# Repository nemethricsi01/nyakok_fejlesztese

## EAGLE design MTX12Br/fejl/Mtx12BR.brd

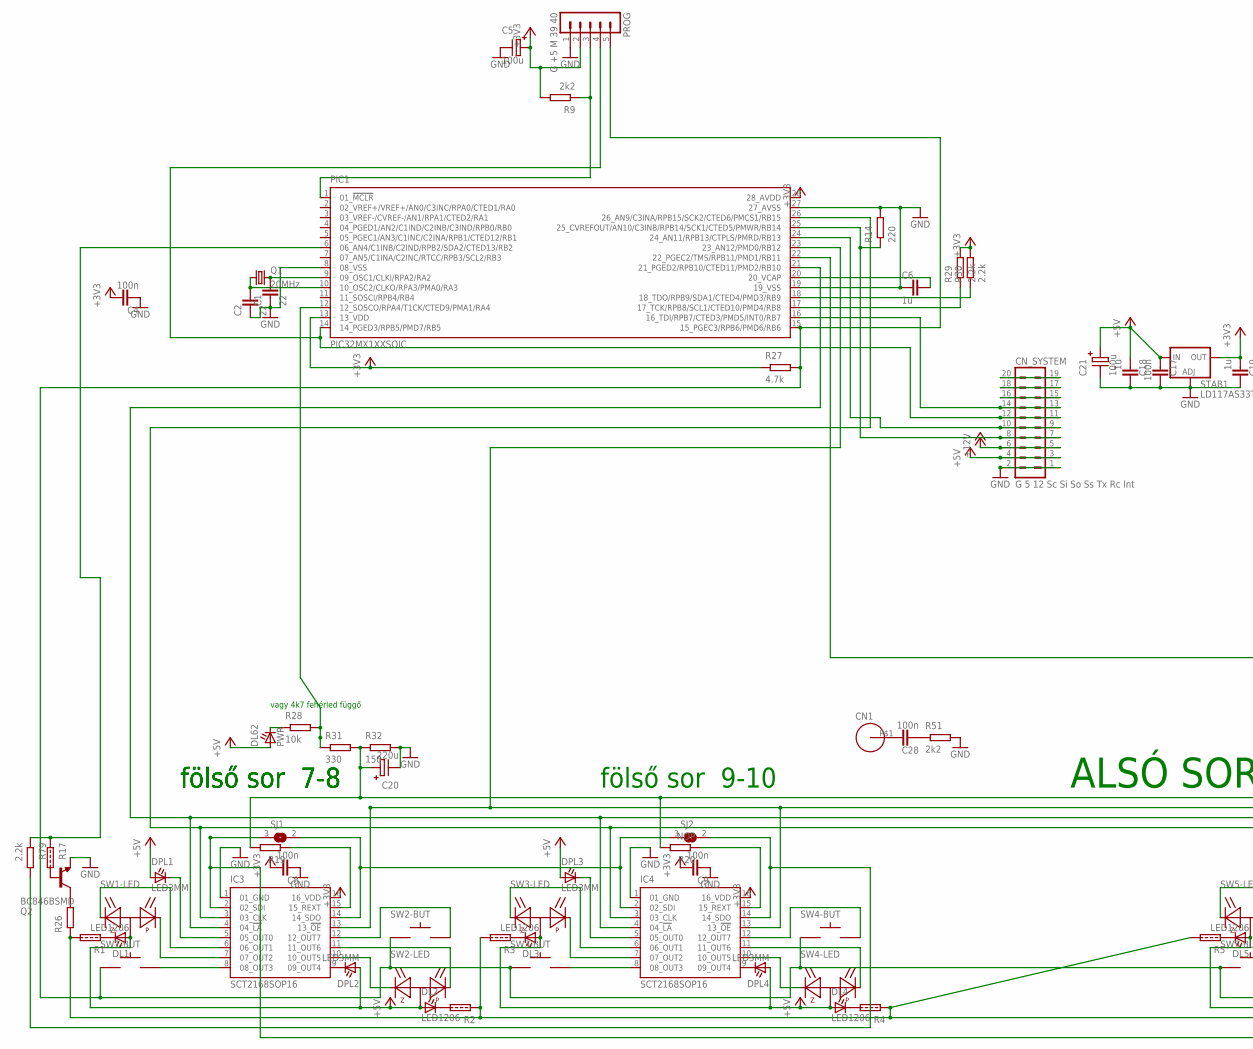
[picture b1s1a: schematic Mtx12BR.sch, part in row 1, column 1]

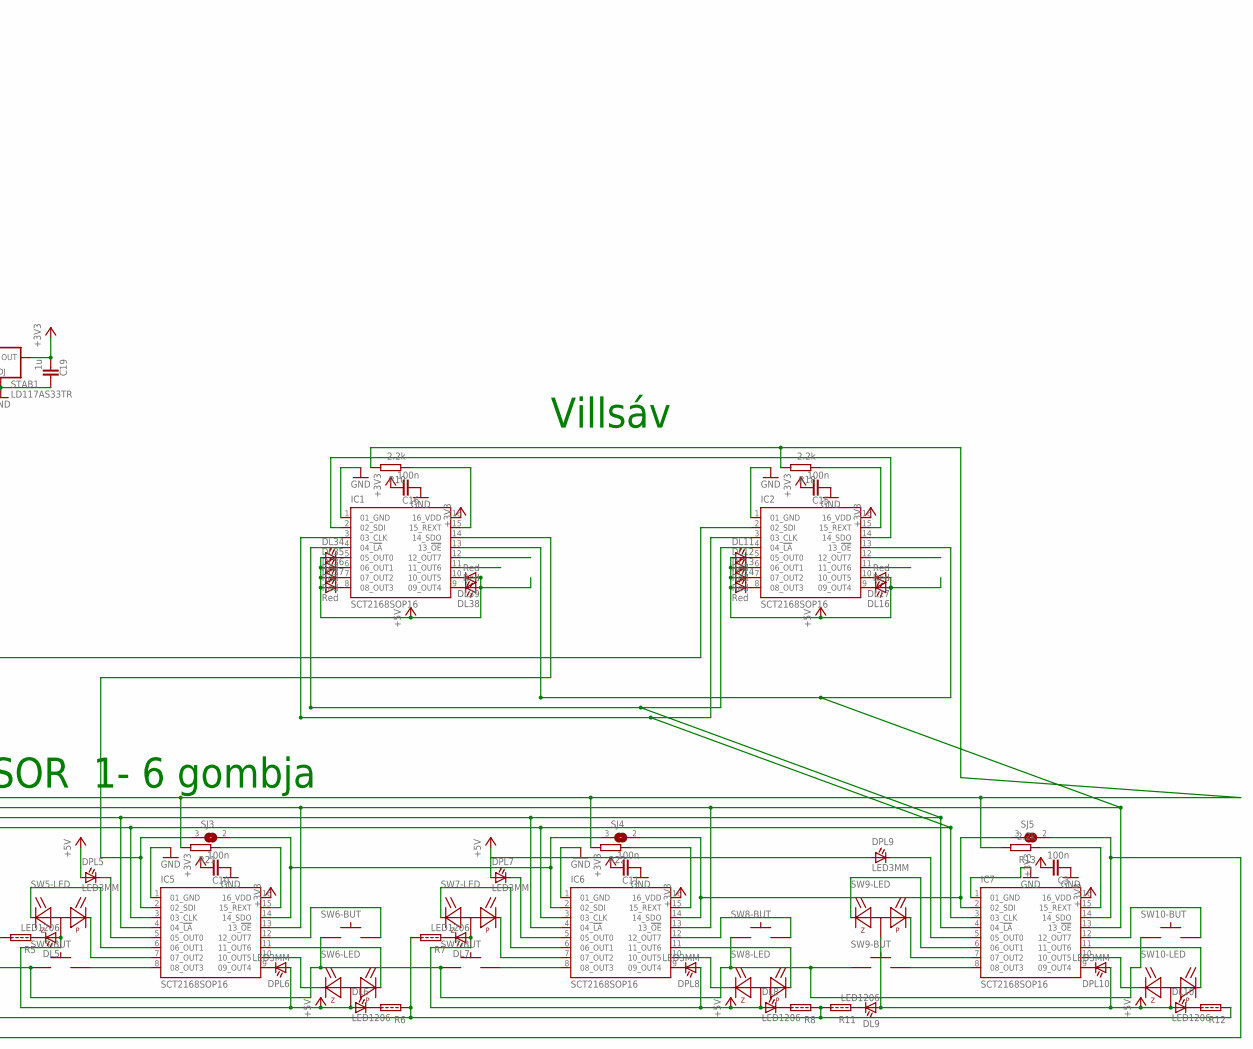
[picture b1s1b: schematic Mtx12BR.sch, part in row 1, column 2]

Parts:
C1, C2: 22; R0805
C3, C4, C8, C9, C10, C11, C15, C16, C17, C28: 100n; R0805
C5, C21: 100u; C_EL1RASZT07
C6, C18, C19: 1u; R0805
C20: 220u; C_EL1RASZT07
CN1: TESTCSAVAR3.5; TESTCSAVAR_3.5
CN_SYSTEM: G 5 12 Sc Si So Ss Tx Rc Int; PIN10_2
DL1, DL2, DL3, DL4, DL5, DL6, DL7, DL8, DL9, DL10: LED1206; R1206
DL11, DL12, DL13, DL14, DL16, DL17, DL34, DL35, DL36, DL37, DL38, DL39: Red; LED5MM
DL62: PWR; LED5MM
DPL1, DPL2, DPL3, DPL4, DPL5, DPL6, DPL7, DPL8, DPL9, DPL10: LED3MM
IC1, IC2, IC3, IC4, IC5, IC6, IC7: SCT2168SOP16; SO16
PIC1: PIC32MX1XXSOIC; SOIC127P1032X265-28N
PROG: G +5 M 39 40; PIN05_1
Q1: 20MHz; XTAL_NAGYSMD
Q2: BC846BSMD; SOT23
R1, R2, R3, R4, R5, R6, R7, R8, R11, R12, R17: RNULL_EU0805; R0805_C
R9, R51: 2k2; R0805
R10, R13, R18, R29, R30, R79: 2.2k; R0805
R14: 220; R0805
R19, R21, R22, R26: R_EU0805; R0805
R20: NOP; R0805
R27: 4.7k; R0805
R28: 10k; R0805
R31: 330; R0805
R32: 150; R0805
SJ1, SJ2, SJ3, SJ4, SJ5: SJ
STAB1: LD117AS33TR; SOT223
SW1, SW2, SW3, SW4, SW5, SW6, SW7, SW8, SW9, SW10: SPG2; SPG2_3LED

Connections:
+3V3: C3.1, C4.1, C5.P+, C8.1, C9.1, C10.1, C11.1, C15.1, C16.1, C19.2, IC1.16 (16_VDD), IC2.16 (16_VDD), IC3.16 (16_VDD), IC4.16 (16_VDD), IC5.16 (16_VDD), IC6.16 (16_VDD), IC7.16 (16_VDD), PIC1.13 (13_VDD), PIC1.28 (28_AVDD), PROG.2, R9.2 (E), R27.1 (A), R29.2 (E), R30.2 (E), STAB1.4 (OUT)
+5V: C17.2, C18.2, C21.P+, CN_SYSTEM.3, CN_SYSTEM.4, DL1.1 (A), DL2.1 (A), DL3.1 (A), DL4.1 (A), DL5.1 (A), DL6.1 (A), DL7.1 (A), DL8.1 (A), DL9.1 (A), DL10.1 (A), DL11.A, DL12.A, DL13.A, DL14.A, DL16.A, DL17.A, DL34.A, DL35.A, DL36.A, DL37.A, DL38.A, DL39.A, DL62.A, DPL1.A, DPL2.A, DPL3.A, DPL4.A, DPL5.A, DPL6.A, DPL7.A, DPL8.A, DPL9.A, DPL10.A, STAB1.3 (IN), SW1.LED+ (+), SW2.LED+ (+), SW3.LED+ (+), SW4.LED+ (+), SW5.LED+ (+), SW6.LED+ (+), SW7.LED+ (+), SW8.LED+ (+), SW9.LED+ (+), SW10.LED+ (+)
+12V: CN_SYSTEM.5, CN_SYSTEM.6
GND: C1.2, C2.2, C3.2, C4.2, C5.P-, C6.2, C8.2, C9.2, C10.2, C11.2, C15.2, C16.2, C17.1, C18.1, C19.1, C20.P-, C21.P-, CN_SYSTEM.1, CN_SYSTEM.2, IC1.1 (01_GND), IC2.1 (01_GND), IC3.1 (01_GND), IC4.1 (01_GND), IC5.1 (01_GND), IC6.1 (01_GND), IC7.1 (01_GND), PIC1.8 (08_VSS), PIC1.19 (19_VSS), PIC1.27 (27_AVSS), PROG.1, Q2.2 (E), R14.2 (E), R32.2 (E), R51.2 (E), STAB1.1 (ADJ)
unnamed: C1.1, PIC1.9 (09_OSC1/CLKI/RPA2/RA2), Q1.P$2 (2)
unnamed: C2.1, PIC1.10 (10_OSC2/CLKO/RPA3/PMA0/RA3), Q1.P$1 (1)
unnamed: C20.P+, R10.2 (E), R13.2 (E), R18.2 (E), R19.2 (E), R20.2 (E), R21.2 (E), R22.2 (E), R31.2 (E), R32.1 (A)
unnamed: IC5.8 (08_OUT3), SW5.G2
unnamed: IC7.7 (07_OUT2), SW9.P-
unnamed: DL34.K (C), IC1.5 (05_OUT0)
unnamed: IC5.7 (07_OUT2), SW5.P-
unnamed: DL35.K (C), IC1.6 (06_OUT1)
unnamed: Q2.1 (B), R17.2 (E)
unnamed: IC5.10 (10_OUT5), SW6.Z- (Z)
unnamed: IC5.6 (06_OUT1), SW5.Z- (Z)
unnamed: IC5.11 (11_OUT6), SW6.P-
unnamed: IC7.6 (06_OUT1), SW9.Z- (Z)
unnamed: IC5.12 (12_OUT7), SW6.G2
unnamed: IC7.10 (10_OUT5), SW10.Z- (Z)
unnamed: IC7.11 (11_OUT6), SW10.P-
unnamed: DPL5.K (C), IC5.5 (05_OUT0)
unnamed: DL6.2 (C), R6.2 (E)
unnamed: DPL6.K (C), IC5.9 (09_OUT4)
unnamed: DL5.2 (C), R5.1 (A)
unnamed: IC2.15 (15_REXT), R18.1 (A)
unnamed: IC7.12 (12_OUT7), SW10.G2
unnamed: DL1.2 (C), R1.1 (A)
unnamed: DPL2.K (C), IC3.9 (09_OUT4)
unnamed: DL2.2 (C), R2.2 (E)
unnamed: IC7.8 (08_OUT3), SW9.G2
unnamed: IC4.7 (07_OUT2), SW3.P-
unnamed: IC4.6 (06_OUT1), SW3.Z- (Z)
unnamed: IC3.7 (07_OUT2), SW1.P-
unnamed: IC3.6 (06_OUT1), SW1.Z- (Z)
unnamed: IC3.10 (10_OUT5), SW2.Z- (Z)
unnamed: IC3.11 (11_OUT6), SW2.P-
unnamed: PIC1.6 (06_AN4/C1INB/C2IND/RPB2/SDA2/CTED13/RB2), R17.1 (A), R79.1 (A)
unnamed: DL62.K (C), R28.1 (A)
unnamed: PIC1.18 (18_TDO/RPB9/SDA1/CTED4/PMD3/RB9), R30.1 (A)
unnamed: PIC1.17 (17_TCK/RPB8/SCL1/CTED10/PMD4/RB8), R29.1 (A)
unnamed: IC1.15 (15_REXT), R10.1 (A)
unnamed: DL36.K (C), IC1.7 (07_OUT2)
unnamed: DL37.K (C), IC1.8 (08_OUT3)
unnamed: DL38.K (C), IC1.9 (09_OUT4)
unnamed: PIC1.1 (01_!MCLR!), PROG.3, R9.1 (A)
unnamed: CN_SYSTEM.15, CN_SYSTEM.16
unnamed: IC3.12 (12_OUT7), SW2.G2
unnamed: CN_SYSTEM.17, CN_SYSTEM.18
unnamed: CN_SYSTEM.19, CN_SYSTEM.20
unnamed: DL39.K (C), IC1.10 (10_OUT5)
unnamed: DPL9.K (C), IC7.5 (05_OUT0)
unnamed: DPL10.K (C), IC7.9 (09_OUT4)
unnamed: IC6.14 (14_SDO), IC7.2 (02_SDI), SJ4.2, SJ5.3 (1)
unnamed: IC3.8 (08_OUT3), SW1.G2
unnamed: DL10.2 (C), R12.2 (E)
unnamed: IC2.2 (02_SDI), PIC1.22 (22_PGEC2/TMS/RPB11/PMD1/RB11)
unnamed: IC1.2 (02_SDI), IC2.14 (14_SDO)
unnamed: DL9.2 (C), R11.1 (A)
unnamed: IC3.2 (02_SDI), IC7.14 (14_SDO), SJ1.3 (1), SJ5.2
unnamed: DPL1.K (C), IC3.5 (05_OUT0)
unnamed: IC4.10 (10_OUT5), SW4.Z- (Z)
unnamed: IC7.15 (15_REXT), R13.1 (A)
unnamed: DL11.K (C), IC2.5 (05_OUT0)
unnamed: C6.1, PIC1.20 (20_VCAP)
unnamed: IC3.14 (14_SDO), IC4.2 (02_SDI), SJ1.2, SJ2.3 (1)
unnamed: IC4.11 (11_OUT6), SW4.P-
unnamed: IC4.12 (12_OUT7), SW4.G2
unnamed: IC4.8 (08_OUT3), SW3.G2
unnamed: DPL3.K (C), IC4.5 (05_OUT0)
unnamed: IC6.7 (07_OUT2), SW7.P-
unnamed: Q2.3 (C), R26.2 (E)
unnamed: PIC1.12 (12_SOSCO/RPA4/T1CK/CTED9/PMA1/RA4), R28.2 (E), R31.1 (A)
unnamed: DL12.K (C), IC2.6 (06_OUT1)
unnamed: IC6.6 (06_OUT1), SW7.Z- (Z)
unnamed: IC6.10 (10_OUT5), SW8.Z- (Z)
unnamed: IC6.11 (11_OUT6), SW8.P-
unnamed: IC6.12 (12_OUT7), SW8.G2
unnamed: IC6.8 (08_OUT3), SW7.G2
unnamed: DPL7.K (C), IC6.5 (05_OUT0)
unnamed: C28.1, CN1.P$1
unnamed: IC4.14 (14_SDO), R79.2 (E), SJ2.2
unnamed: DPL4.K (C), IC4.9 (09_OUT4)
unnamed: DL3.2 (C), R3.1 (A)
unnamed: DL4.2 (C), R4.2 (E)
unnamed: IC3.15 (15_REXT), R19.1 (A)
unnamed: DL13.K (C), IC2.7 (07_OUT2)
unnamed: IC4.15 (15_REXT), R20.1 (A)
unnamed: IC5.15 (15_REXT), R21.1 (A)
unnamed: IC6.15 (15_REXT), R22.1 (A)
unnamed: DL14.K (C), IC2.8 (08_OUT3)
unnamed: DL16.K (C), IC2.9 (09_OUT4)
unnamed: DL17.K (C), IC2.10 (10_OUT5)
unnamed: DPL8.K (C), IC6.9 (09_OUT4)
unnamed: DL7.2 (C), R7.1 (A)
unnamed: DL8.2 (C), R8.2 (E)
unnamed: C28.2, R51.1 (A)
unnamed: IC5.14 (14_SDO), IC6.2 (02_SDI), SJ3.2, SJ4.3 (1)
unnamed: R1.2 (E), R2.1 (A), R3.2 (E), R4.1 (A), R5.2 (E), R6.1 (A), R7.2 (E), R8.1 (A), R11.2 (E), R12.1 (A), R26.1 (A)
unnamed: IC1.13 (13_!OE!), IC2.13 (13_!OE!), IC3.13 (13_!OE!), IC4.13 (13_!OE!), IC5.13 (13_!OE!), IC6.13 (13_!OE!), IC7.13 (13_!OE!), PIC1.23 (23_AN12/PMD0/RB12)
SCK1: CN_SYSTEM.7, CN_SYSTEM.8, PIC1.25 (25_CVREFOUT/AN10/C3INB/RPB14/SCK1/CTED5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), R14.1 (A)
SCK3: IC1.3 (03_CLK), IC2.3 (03_CLK), IC3.3 (03_CLK), IC4.3 (03_CLK), IC5.3 (03_CLK), IC6.3 (03_CLK), IC7.3 (03_CLK), PIC1.26 (26_AN9/C3INA/RPB15/SCK2/CTED6/PMCS1/RB15)
SDI1: CN_SYSTEM.11, CN_SYSTEM.12, PIC1.14 (14_PGED3/RPB5/PMD7/RB5), PROG.4
SDI3: PIC1.15 (15_PGEC3/RPB6/PMD6/RB6), PROG.5, R27.2 (E), SW1.G1, SW2.G1, SW3.G1, SW4.G1, SW5.G1, SW6.G1, SW7.G1, SW8.G1, SW9.G1, SW10.G1
SDO1: CN_SYSTEM.9, CN_SYSTEM.10, PIC1.24 (24_AN11/RPB13/CTPLS/PMRD/RB13)
SDO2: IC1.14 (14_SDO), IC5.2 (02_SDI), SJ3.3 (1)
SS1: CN_SYSTEM.13, CN_SYSTEM.14, PIC1.16 (16_TDI/RPB7/CTED3/PMD5/INT0/RB7)
SS3: IC1.4 (04_!LA!), IC2.4 (04_!LA!), IC3.4 (04_!LA!), IC4.4 (04_!LA!), IC5.4 (04_!LA!), IC6.4 (04_!LA!), IC7.4 (04_!LA!), PIC1.21 (21_PGED2/RPB10/CTED11/PMD2/RB10)

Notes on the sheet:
ALSÓ SOR 1- 6 gombja
fölső sor 7-8
fölső sor 9-10
Villsáv
vagy 4k7 fehérled függő

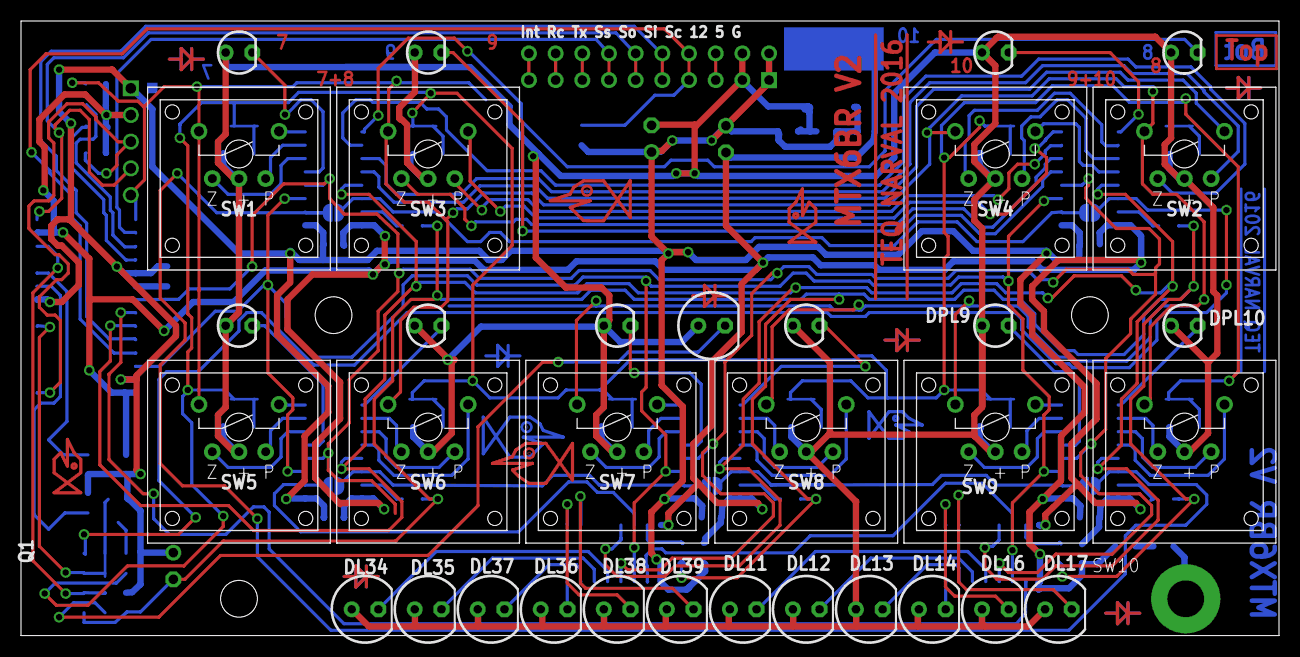
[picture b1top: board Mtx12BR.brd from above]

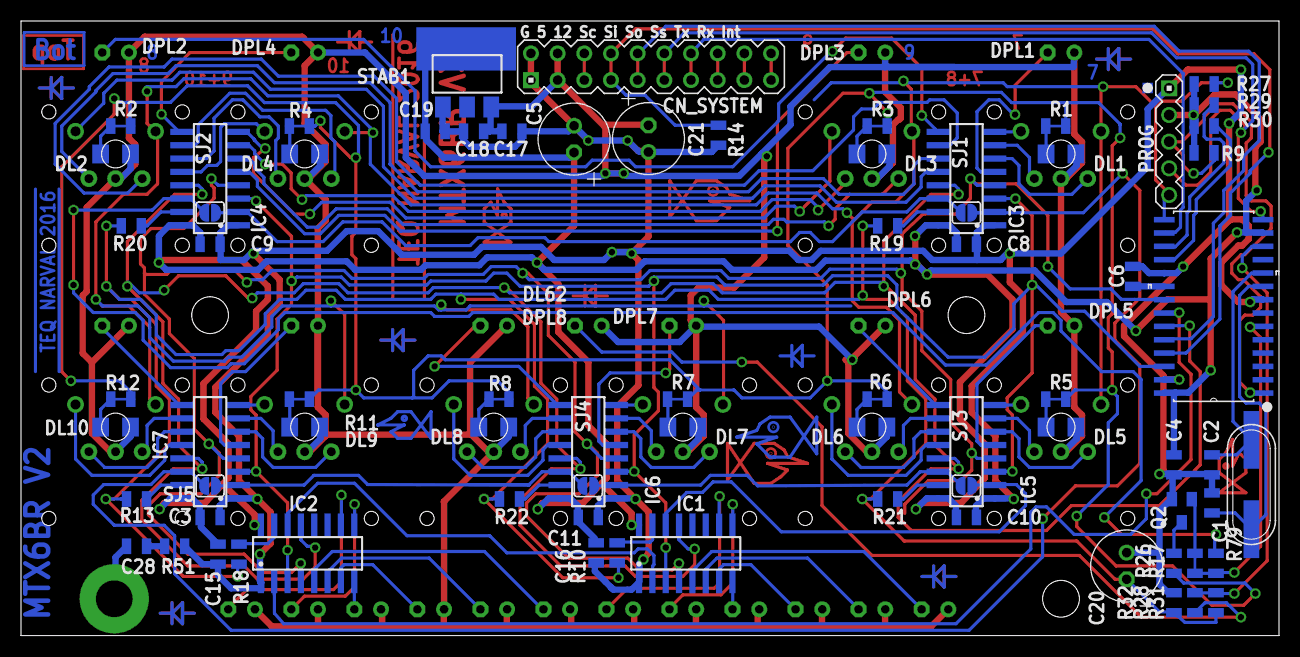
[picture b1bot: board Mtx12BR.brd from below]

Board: 2 copper layers, 119.8 x 58.5 mm, 109 parts (75 on the bottom side), 107 nets.

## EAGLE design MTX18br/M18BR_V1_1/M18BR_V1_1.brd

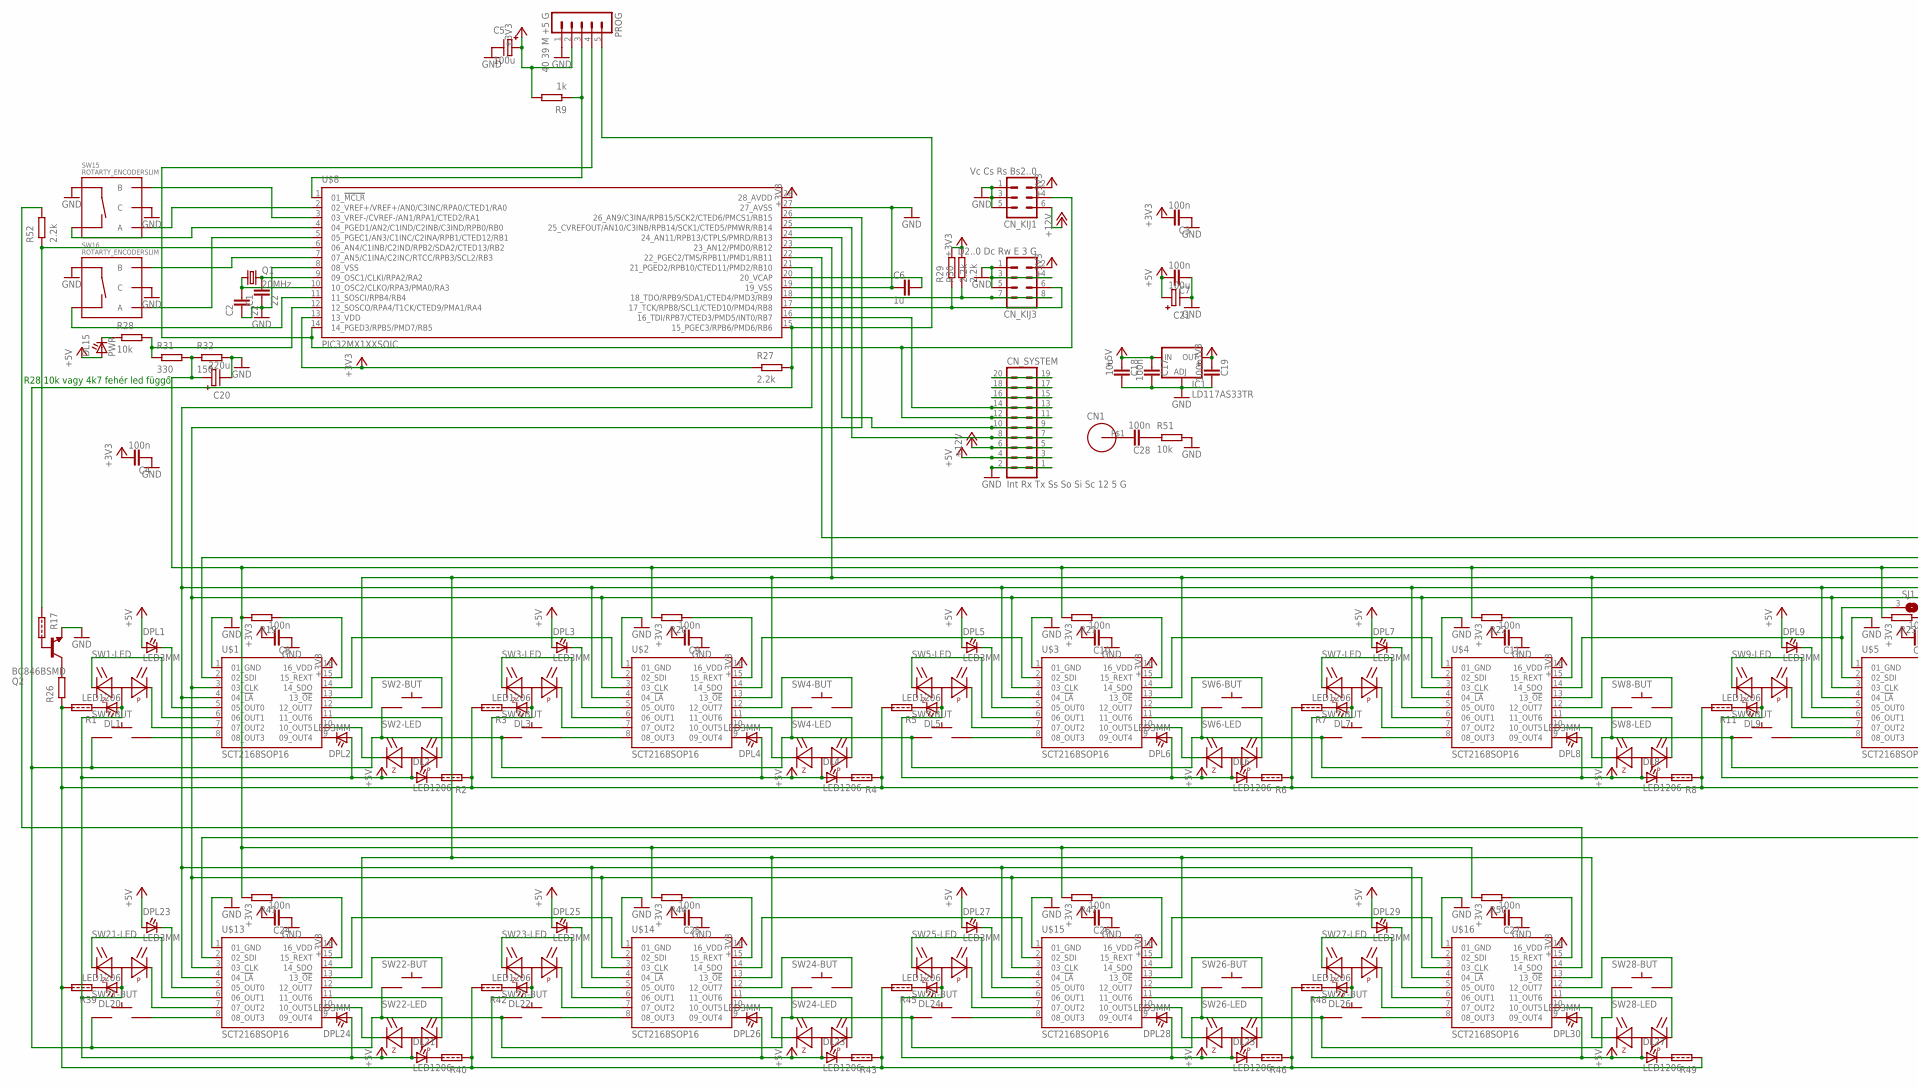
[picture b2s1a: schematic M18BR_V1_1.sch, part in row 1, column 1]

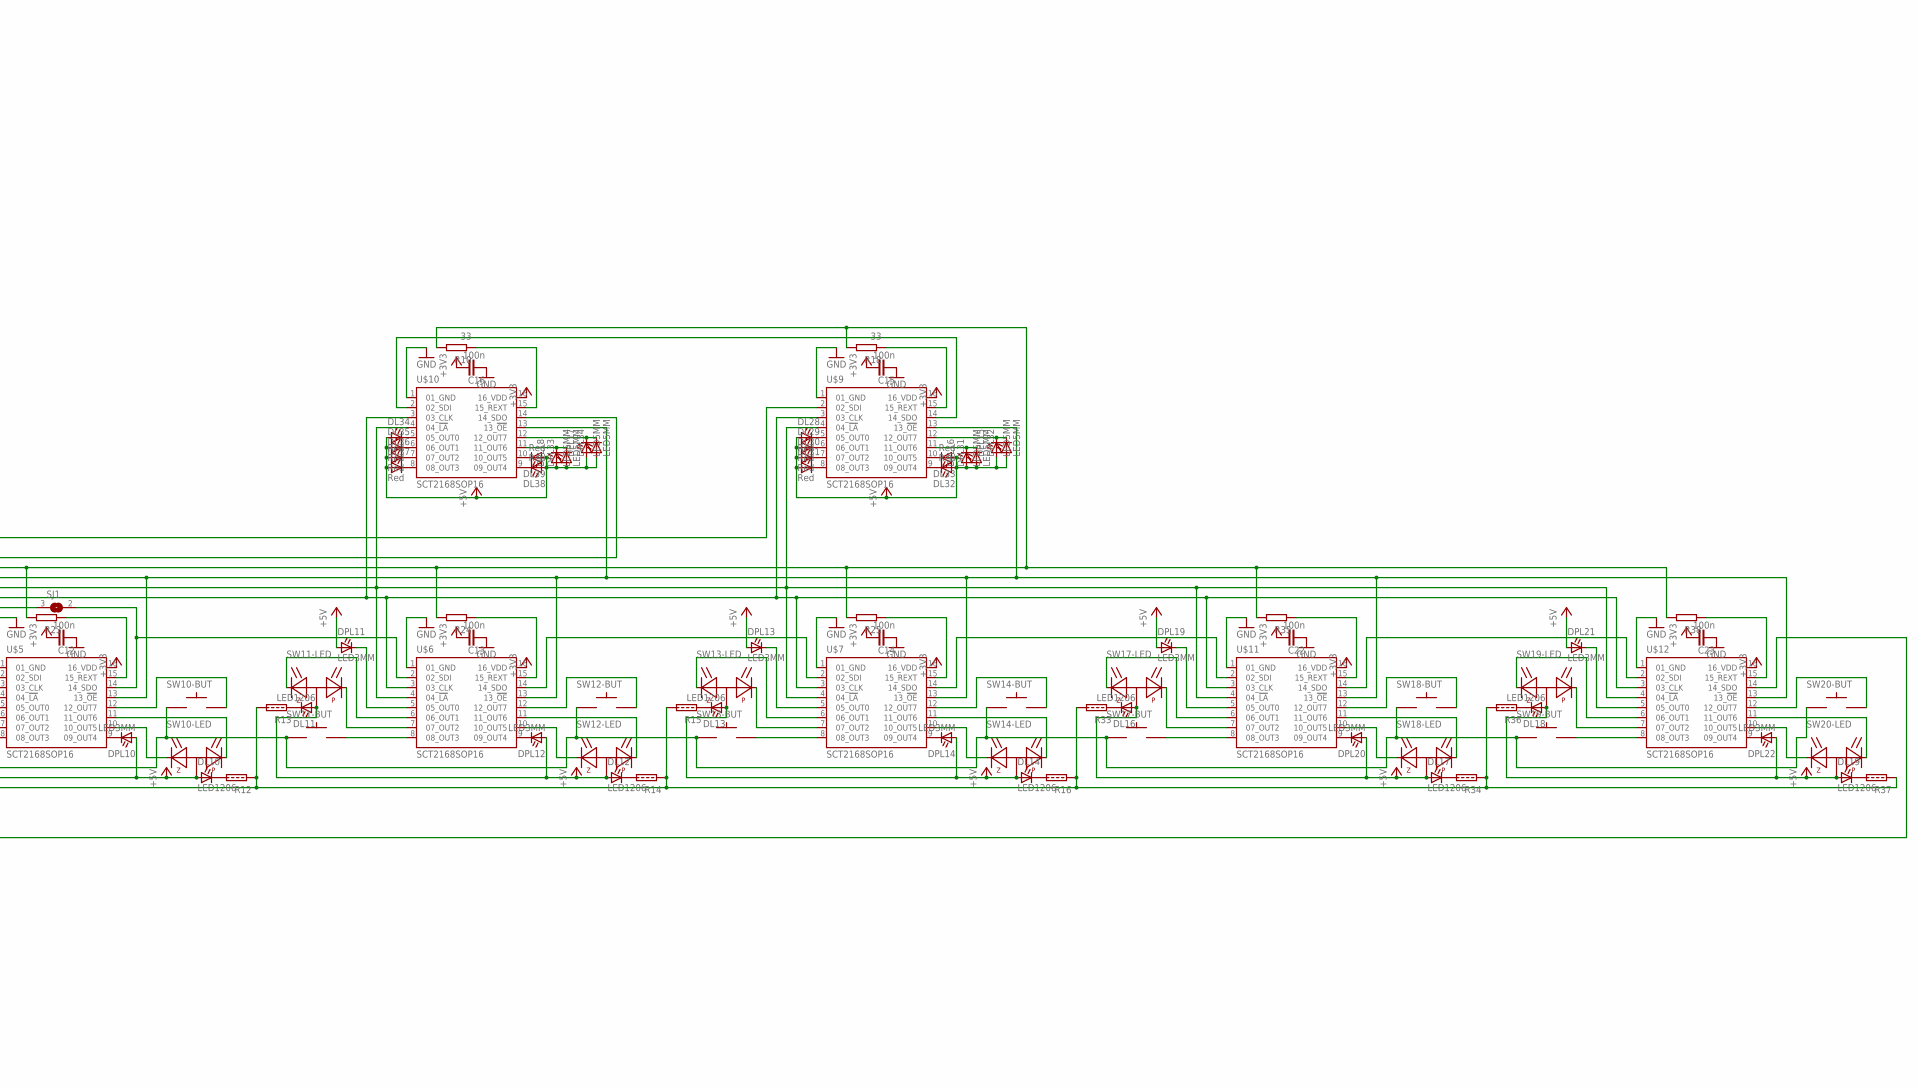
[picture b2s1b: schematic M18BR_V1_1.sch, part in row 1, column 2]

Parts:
C1, C2: 22; R0805
C3, C4, C7, C8, C9, C10, C11, C12, C13, C14, C15, C16, C17, C19, C22, C23, C24, C25, C26, C27, C28: 100n; R0805
C5, C21: 100u; C_EL1RASZT07
C6: 1u; R0805
C18: 10u; R0805
C20: 220u; C_EL1RASZT07
CN1: TESTCSAVAR
CN_KIJ1: Vc Cs Rs Bs2..0; PIN03_2
CN_KIJ3: D2..0 Dc Rw E 3 G; PIN04_2
CN_SYSTEM: Int Rx Tx Ss So Si Sc 12 5 G; PIN10_2
DL1, DL2, DL3, DL4, DL5, DL6, DL7, DL8, DL9, DL10, DL11, DL12, DL13, DL14, DL16, DL17, DL18, DL19, DL20, DL21, DL22, DL23, DL24, DL25, DL26, DL27: LED1206; R1206
DL15: PWR; LED5MM
DL28, DL29, DL30, DL31, DL32, DL33, DL34, DL35, DL36, DL37, DL38, DL39: Red; LED5MM
DPL1, DPL2, DPL3, DPL4, DPL5, DPL6, DPL7, DPL8, DPL9, DPL10, DPL11, DPL12, DPL13, DPL14, DPL19, DPL20, DPL21, DPL22, DPL23, DPL24, DPL25, DPL26, DPL27, DPL28, DPL29, DPL30: LED3MM
DPL15, DPL16, DPL17, DPL18, DPL31, DPL32, DPL33, DPL34: LED5MM
IC1: LD117AS33TR; SOT223
PROG: 40 39 M +5 G; PIN05_1
Q1: 20MHz; XTAL_QS
Q2: BC846BSMD; SOT23
R1, R2, R3, R4, R5, R6, R7, R8, R11, R12, R13, R14, R15, R16, R17, R33, R34, R36, R37, R39, R40, R42, R43, R45, R46, R48, R49: RNULL_EU0805; R0805_C
R9: 1k; R0805
R10, R18: 33; R0805
R19, R20, R21, R22, R23, R24, R25, R26, R35, R38, R41, R44, R47, R50: R_EU0805; R0805
R27, R29, R30, R52: 2.2k; R0805
R28, R51: 10k; R0805
R31: 330; R0805
R32: 150; R0805
SJ1: SJ
SW1, SW2, SW3, SW4, SW5, SW6, SW7, SW8, SW9, SW10, SW11, SW12, SW13, SW14, SW17, SW18, SW19, SW20, SW21, SW22, SW23, SW24, SW25, SW26, SW27, SW28: SPG2; SPG2_3LED
SW15, SW16: ROTARTY_ENCODERSLIM; ROTARY_ENC_SLIM
U$1, U$2, U$3, U$4, U$5, U$6, U$7, U$9, U$10, U$11, U$12, U$13, U$14, U$15, U$16: SCT2168SOP16; SO16
U$8: PIC32MX1XXSOIC; SOIC127P1032X265-28N

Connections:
+3V3: C3.1, C4.1, C5.P+, C8.1, C9.1, C10.1, C11.1, C12.1, C13.1, C14.1, C15.1, C16.1, C19.2, C22.1, C23.1, C24.1, C25.1, C26.1, C27.1, CN_KIJ1.2, CN_KIJ3.2, DL15.A, IC1.4 (OUT), PROG.2, R9.2 (E), R27.1 (A), R29.2 (E), R30.2 (E), U$1.16 (16_VDD), U$2.16 (16_VDD), U$3.16 (16_VDD), U$4.16 (16_VDD), U$5.16 (16_VDD), U$6.16 (16_VDD), U$7.16 (16_VDD), U$8.13 (13_VDD), U$8.28 (28_AVDD), U$9.16 (16_VDD), U$10.16 (16_VDD), U$11.16 (16_VDD), U$12.16 (16_VDD), U$13.16 (16_VDD), U$14.16 (16_VDD), U$15.16 (16_VDD), U$16.16 (16_VDD)
+5V: C7.1, C17.2, C18.2, C21.P+, CN_SYSTEM.3, CN_SYSTEM.4, DL1.1 (A), DL2.1 (A), DL3.1 (A), DL4.1 (A), DL5.1 (A), DL6.1 (A), DL7.1 (A), DL8.1 (A), DL9.1 (A), DL10.1 (A), DL11.1 (A), DL12.1 (A), DL13.1 (A), DL14.1 (A), DL16.1 (A), DL17.1 (A), DL18.1 (A), DL19.1 (A), DL20.1 (A), DL21.1 (A), DL22.1 (A), DL23.1 (A), DL24.1 (A), DL25.1 (A), DL26.1 (A), DL27.1 (A), DL28.A, DL29.A, DL30.A, DL31.A, DL32.A, DL33.A, DL34.A, DL35.A, DL36.A, DL37.A, DL38.A, DL39.A, DPL1.A, DPL2.A, DPL3.A, DPL4.A, DPL5.A, DPL6.A, DPL7.A, DPL8.A, DPL9.A, DPL10.A, DPL11.A, DPL12.A, DPL13.A, DPL14.A, DPL15.A, DPL16.A, DPL17.A, DPL18.A, DPL19.A, DPL20.A, DPL21.A, DPL22.A, DPL23.A, DPL24.A, DPL25.A, DPL26.A, DPL27.A, DPL28.A, DPL29.A, DPL30.A, DPL31.A, DPL32.A, DPL33.A, DPL34.A, IC1.3 (IN), SW1.LED+ (+), SW2.LED+ (+), SW3.LED+ (+), SW4.LED+ (+), SW5.LED+ (+), SW6.LED+ (+), SW7.LED+ (+), SW8.LED+ (+), SW9.LED+ (+), SW10.LED+ (+), SW11.LED+ (+), SW12.LED+ (+), SW13.LED+ (+), SW14.LED+ (+), SW17.LED+ (+), SW18.LED+ (+), SW19.LED+ (+), SW20.LED+ (+), SW21.LED+ (+), SW22.LED+ (+), SW23.LED+ (+), SW24.LED+ (+), SW25.LED+ (+), SW26.LED+ (+), SW27.LED+ (+), SW28.LED+ (+)
+12V: CN_KIJ1.6, CN_SYSTEM.5, CN_SYSTEM.6
GND: C1.2, C2.2, C3.2, C4.2, C5.P-, C6.2, C7.2, C8.2, C9.2, C10.2, C11.2, C12.2, C13.2, C14.2, C15.2, C16.2, C17.1, C18.1, C19.1, C20.P-, C21.P-, C22.2, C23.2, C24.2, C25.2, C26.2, C27.2, CN_KIJ1.1, CN_KIJ1.3, CN_KIJ1.5, CN_KIJ3.1, CN_KIJ3.3, CN_KIJ3.4, CN_KIJ3.5, CN_SYSTEM.1, CN_SYSTEM.2, IC1.1 (ADJ), PROG.1, Q2.2 (E), R32.2 (E), R51.2 (E), SW15.C, SW15.SW+, SW16.C, SW16.SW+, U$1.1 (01_GND), U$2.1 (01_GND), U$3.1 (01_GND), U$4.1 (01_GND), U$5.1 (01_GND), U$6.1 (01_GND), U$7.1 (01_GND), U$8.8 (08_VSS), U$8.19 (19_VSS), U$8.27 (27_AVSS), U$9.1 (01_GND), U$10.1 (01_GND), U$11.1 (01_GND), U$12.1 (01_GND), U$13.1 (01_GND), U$14.1 (01_GND), U$15.1 (01_GND), U$16.1 (01_GND)
unnamed: C1.1, Q1.2, U$8.9 (09_OSC1/CLKI/RPA2/RA2)
unnamed: C2.1, Q1.1, U$8.10 (10_OSC2/CLKO/RPA3/PMA0/RA3)
unnamed: DL28.K (C), U$9.5 (05_OUT0)
unnamed: SW5.G2, U$3.8 (08_OUT3)
unnamed: DL29.K (C), U$9.6 (06_OUT1)
unnamed: DL34.K (C), U$10.5 (05_OUT0)
unnamed: SW5.P-, U$3.7 (07_OUT2)
unnamed: DL35.K (C), U$10.6 (06_OUT1)
unnamed: Q2.1 (B), R17.2 (E)
unnamed: SW6.Z- (Z), U$3.10 (10_OUT5)
unnamed: SW5.Z- (Z), U$3.6 (06_OUT1)
unnamed: SW6.P-, U$3.11 (11_OUT6)
unnamed: SW15.B, U$8.3 (03_VREF-/CVREF-/AN1/RPA1/CTED2/RA1)
unnamed: SW6.G2, U$3.12 (12_OUT7)
unnamed: DL14.2 (C), R16.2 (E)
unnamed: DPL5.K (C), U$3.5 (05_OUT0)
unnamed: DL6.2 (C), R6.2 (E)
unnamed: DPL6.K (C), U$3.9 (09_OUT4)
unnamed: DL5.2 (C), R5.1 (A)
unnamed: R18.1 (A), U$9.15 (15_REXT)
unnamed: SW15.A, U$8.2 (02_VREF+/VREF+/AN0/C3INC/RPA0/CTED1/RA0)
unnamed: DL1.2 (C), R1.1 (A)
unnamed: DPL2.K (C), U$1.9 (09_OUT4)
unnamed: DL2.2 (C), R2.2 (E)
unnamed: R1.2 (E), R2.1 (A), R3.2 (E), R4.1 (A), R5.2 (E), R6.1 (A), R7.2 (E), R8.1 (A), R11.2 (E), R12.1 (A), R13.2 (E), R14.1 (A), R15.2 (E), R16.1 (A), R26.1 (A), R33.2 (E), R34.1 (A), R36.2 (E), R37.1 (A), R39.2 (E), R40.1 (A), R42.2 (E), R43.1 (A), R45.2 (E), R46.1 (A), R48.2 (E), R49.1 (A)
unnamed: SW3.P-, U$2.7 (07_OUT2)
unnamed: SW3.Z- (Z), U$2.6 (06_OUT1)
unnamed: SW1.P-, U$1.7 (07_OUT2)
unnamed: SW1.Z- (Z), U$1.6 (06_OUT1)
unnamed: SW2.Z- (Z), U$1.10 (10_OUT5)
unnamed: SW2.P-, U$1.11 (11_OUT6)
unnamed: R17.1 (A), R52.1 (A), U$8.6 (06_AN4/C1INB/C2IND/RPB2/SDA2/CTED13/RB2)
unnamed: DL15.K (C), R28.1 (A)
unnamed: CN_KIJ3.7, CN_KIJ3.8, R30.1 (A), U$8.18 (18_TDO/RPB9/SDA1/CTED4/PMD3/RB9)
unnamed: CN_KIJ3.6, R29.1 (A), U$8.17 (17_TCK/RPB8/SCL1/CTED10/PMD4/RB8)
unnamed: R10.1 (A), U$10.15 (15_REXT)
unnamed: DL36.K (C), U$10.7 (07_OUT2)
unnamed: DL37.K (C), U$10.8 (08_OUT3)
unnamed: DL38.K (C), U$10.9 (09_OUT4)
unnamed: PROG.3, R9.1 (A), U$8.1 (01_!MCLR!)
unnamed: CN_SYSTEM.15, CN_SYSTEM.16
unnamed: SW2.G2, U$1.12 (12_OUT7)
unnamed: CN_SYSTEM.17, CN_SYSTEM.18
unnamed: CN_SYSTEM.19, CN_SYSTEM.20
unnamed: DL39.K (C), U$10.10 (10_OUT5)
unnamed: DL30.K (C), U$9.7 (07_OUT2)
unnamed: DL31.K (C), U$9.8 (08_OUT3)
unnamed: DL32.K (C), U$9.9 (09_OUT4)
unnamed: SW1.G2, U$1.8 (08_OUT3)
unnamed: DL33.K (C), U$9.10 (10_OUT5)
unnamed: DPL16.K (C), DPL31.K (C), U$9.11 (11_OUT6)
unnamed: U$8.22 (22_PGEC2/TMS/RPB11/PMD1/RB11), U$9.2 (02_SDI)
unnamed: U$9.14 (14_SDO), U$10.2 (02_SDI)
unnamed: DPL15.K (C), DPL32.K (C), U$9.12 (12_OUT7)
unnamed: SW16.B, U$8.7 (07_AN5/C1INA/C2INC/RTCC/RPB3/SCL2/RB3)
unnamed: SW16.A, U$8.5 (05_PGEC1/AN3/C1INC/C2INA/RPB1/CTED12/RB1)
unnamed: DPL1.K (C), U$1.5 (05_OUT0)
unnamed: SW4.Z- (Z), U$2.10 (10_OUT5)
unnamed: SW15.SW-, U$8.4 (04_PGED1/AN2/C1IND/C2INB/C3IND/RPB0/RB0)
unnamed: SW16.SW-, U$8.11 (11_SOSCI/RPB4/RB4)
unnamed: C6.1, U$8.20 (20_VCAP)
unnamed: U$1.14 (14_SDO), U$2.2 (02_SDI)
unnamed: SW4.P-, U$2.11 (11_OUT6)
unnamed: SW4.G2, U$2.12 (12_OUT7)
unnamed: SW3.G2, U$2.8 (08_OUT3)
unnamed: DPL3.K (C), U$2.5 (05_OUT0)
unnamed: DPL17.K (C), DPL34.K (C), U$10.12 (12_OUT7)
unnamed: DPL18.K (C), DPL33.K (C), U$10.11 (11_OUT6)
unnamed: SW7.P-, U$4.7 (07_OUT2)
unnamed: Q2.3 (C), R26.2 (E)
unnamed: R28.2 (E), R31.1 (A), U$8.12 (12_SOSCO/RPA4/T1CK/CTED9/PMA1/RA4)
unnamed: C20.P+, R10.2 (E), R18.2 (E), R19.2 (E), R20.2 (E), R21.2 (E), R22.2 (E), R23.2 (E), R24.2 (E), R25.2 (E), R31.2 (E), R32.1 (A), R35.2 (E), R38.2 (E), R41.2 (E), R44.2 (E), R47.2 (E), R50.2 (E)
unnamed: SW7.Z- (Z), U$4.6 (06_OUT1)
unnamed: SW8.Z- (Z), U$4.10 (10_OUT5)
unnamed: SW8.P-, U$4.11 (11_OUT6)
unnamed: SW8.G2, U$4.12 (12_OUT7)
unnamed: SW7.G2, U$4.8 (08_OUT3)
unnamed: DPL7.K (C), U$4.5 (05_OUT0)
unnamed: C28.1, CN1.P$1
unnamed: U$2.14 (14_SDO), U$3.2 (02_SDI)
unnamed: DPL4.K (C), U$2.9 (09_OUT4)
unnamed: DL3.2 (C), R3.1 (A)
unnamed: DL4.2 (C), R4.2 (E)
unnamed: R19.1 (A), U$1.15 (15_REXT)
unnamed: SW9.P-, U$5.7 (07_OUT2)
unnamed: R20.1 (A), U$2.15 (15_REXT)
unnamed: R21.1 (A), U$3.15 (15_REXT)
unnamed: R22.1 (A), U$4.15 (15_REXT)
unnamed: SW9.Z- (Z), U$5.6 (06_OUT1)
unnamed: SW10.Z- (Z), U$5.10 (10_OUT5)
unnamed: SW10.P-, U$5.11 (11_OUT6)
unnamed: SW10.G2, U$5.12 (12_OUT7)
unnamed: SW9.G2, U$5.8 (08_OUT3)
unnamed: DPL9.K (C), U$5.5 (05_OUT0)
unnamed: SW17.P-, U$11.7 (07_OUT2)
unnamed: U$3.14 (14_SDO), U$4.2 (02_SDI)
unnamed: R23.1 (A), U$5.15 (15_REXT)
unnamed: DPL8.K (C), U$4.9 (09_OUT4)
unnamed: DL7.2 (C), R7.1 (A)
unnamed: DL8.2 (C), R8.2 (E)
unnamed: R52.2 (E), U$16.14 (14_SDO)
unnamed: SW17.Z- (Z), U$11.6 (06_OUT1)
unnamed: SW18.Z- (Z), U$11.10 (10_OUT5)
unnamed: SW18.P-, U$11.11 (11_OUT6)
unnamed: SW18.G2, U$11.12 (12_OUT7)
unnamed: SW17.G2, U$11.8 (08_OUT3)
unnamed: SW11.P-, U$6.7 (07_OUT2)
unnamed: SW11.Z- (Z), U$6.6 (06_OUT1)
unnamed: SW12.Z- (Z), U$6.10 (10_OUT5)
unnamed: SW12.P-, U$6.11 (11_OUT6)
unnamed: SW12.G2, U$6.12 (12_OUT7)
unnamed: SW11.G2, U$6.8 (08_OUT3)
unnamed: DPL11.K (C), U$6.5 (05_OUT0)
unnamed: DPL19.K (C), U$11.5 (05_OUT0)
unnamed: SJ1.3 (1), U$4.14 (14_SDO), U$5.2 (02_SDI)
unnamed: R24.1 (A), U$6.15 (15_REXT)
unnamed: DPL20.K (C), U$11.9 (09_OUT4)
unnamed: SW13.P-, U$7.7 (07_OUT2)
unnamed: DL16.2 (C), R33.1 (A)
unnamed: SW13.Z- (Z), U$7.6 (06_OUT1)
unnamed: DL17.2 (C), R34.2 (E)
unnamed: R35.1 (A), U$11.15 (15_REXT)
unnamed: SW14.Z- (Z), U$7.10 (10_OUT5)
unnamed: SW14.P-, U$7.11 (11_OUT6)
unnamed: SW14.G2, U$7.12 (12_OUT7)
unnamed: SW13.G2, U$7.8 (08_OUT3)
unnamed: DPL13.K (C), U$7.5 (05_OUT0)
unnamed: U$11.14 (14_SDO), U$12.2 (02_SDI)
unnamed: C28.2, R51.1 (A)
unnamed: R25.1 (A), U$7.15 (15_REXT)
unnamed: U$1.13 (13_!OE!), U$2.13 (13_!OE!), U$3.13 (13_!OE!), U$4.13 (13_!OE!), U$5.13 (13_!OE!), U$6.13 (13_!OE!), U$7.13 (13_!OE!), U$8.23 (23_AN12/PMD0/RB12), U$9.13 (13_!OE!), U$10.13 (13_!OE!), U$11.13 (13_!OE!), U$12.13 (13_!OE!), U$13.13 (13_!OE!), U$14.13 (13_!OE!), U$15.13 (13_!OE!), U$16.13 (13_!OE!)
unnamed: DPL10.K (C), U$5.9 (09_OUT4)
unnamed: DPL12.K (C), U$6.9 (09_OUT4)
unnamed: DPL14.K (C), U$7.9 (09_OUT4)
unnamed: DL13.2 (C), R15.1 (A)
unnamed: DL12.2 (C), R14.2 (E)
unnamed: U$6.14 (14_SDO), U$7.2 (02_SDI)
unnamed: SW21.P-, U$13.7 (07_OUT2)
unnamed: SW21.Z- (Z), U$13.6 (06_OUT1)
unnamed: SJ1.2, U$5.14 (14_SDO), U$6.2 (02_SDI)
unnamed: SW22.Z- (Z), U$13.10 (10_OUT5)
unnamed: SW22.P-, U$13.11 (11_OUT6)
unnamed: SW22.G2, U$13.12 (12_OUT7)
unnamed: SW21.G2, U$13.8 (08_OUT3)
unnamed: DPL23.K (C), U$13.5 (05_OUT0)
unnamed: DPL24.K (C), U$13.9 (09_OUT4)
unnamed: DL20.2 (C), R39.1 (A)
unnamed: DL21.2 (C), R40.2 (E)
unnamed: R41.1 (A), U$13.15 (15_REXT)
unnamed: U$12.14 (14_SDO), U$13.2 (02_SDI)
unnamed: U$13.14 (14_SDO), U$14.2 (02_SDI)
unnamed: SW19.P-, U$12.7 (07_OUT2)
unnamed: SW19.Z- (Z), U$12.6 (06_OUT1)
unnamed: SW20.Z- (Z), U$12.10 (10_OUT5)
unnamed: SW23.P-, U$14.7 (07_OUT2)
unnamed: SW23.Z- (Z), U$14.6 (06_OUT1)
unnamed: SW24.Z- (Z), U$14.10 (10_OUT5)
unnamed: SW24.P-, U$14.11 (11_OUT6)
unnamed: SW24.G2, U$14.12 (12_OUT7)
unnamed: SW23.G2, U$14.8 (08_OUT3)
unnamed: DPL25.K (C), U$14.5 (05_OUT0)
unnamed: DPL26.K (C), U$14.9 (09_OUT4)
unnamed: DL22.2 (C), R42.1 (A)
unnamed: DL23.2 (C), R43.2 (E)
unnamed: R44.1 (A), U$14.15 (15_REXT)
unnamed: SW20.P-, U$12.11 (11_OUT6)
unnamed: U$14.14 (14_SDO), U$15.2 (02_SDI)
unnamed: SW20.G2, U$12.12 (12_OUT7)
unnamed: SW19.G2, U$12.8 (08_OUT3)
unnamed: DPL21.K (C), U$12.5 (05_OUT0)
unnamed: SW25.P-, U$15.7 (07_OUT2)
unnamed: SW25.Z- (Z), U$15.6 (06_OUT1)
unnamed: SW26.Z- (Z), U$15.10 (10_OUT5)
unnamed: SW26.P-, U$15.11 (11_OUT6)
unnamed: SW26.G2, U$15.12 (12_OUT7)
unnamed: SW25.G2, U$15.8 (08_OUT3)
unnamed: DPL27.K (C), U$15.5 (05_OUT0)
unnamed: DPL28.K (C), U$15.9 (09_OUT4)
unnamed: DL24.2 (C), R45.1 (A)
unnamed: DL25.2 (C), R46.2 (E)
unnamed: R47.1 (A), U$15.15 (15_REXT)
unnamed: DPL22.K (C), U$12.9 (09_OUT4)
unnamed: U$15.14 (14_SDO), U$16.2 (02_SDI)
unnamed: DL18.2 (C), R36.1 (A)
unnamed: DL19.2 (C), R37.2 (E)
unnamed: DL11.2 (C), R13.1 (A)
unnamed: SW27.P-, U$16.7 (07_OUT2)
unnamed: SW27.Z- (Z), U$16.6 (06_OUT1)
unnamed: SW28.Z- (Z), U$16.10 (10_OUT5)
unnamed: SW28.P-, U$16.11 (11_OUT6)
unnamed: SW28.G2, U$16.12 (12_OUT7)
unnamed: SW27.G2, U$16.8 (08_OUT3)
unnamed: DPL29.K (C), U$16.5 (05_OUT0)
unnamed: DPL30.K (C), U$16.9 (09_OUT4)
unnamed: DL26.2 (C), R48.1 (A)
unnamed: DL27.2 (C), R49.2 (E)
unnamed: R50.1 (A), U$16.15 (15_REXT)
unnamed: R38.1 (A), U$12.15 (15_REXT)
unnamed: DL10.2 (C), R12.2 (E)
unnamed: U$7.14 (14_SDO), U$11.2 (02_SDI)
unnamed: DL9.2 (C), R11.1 (A)
SCK1: CN_SYSTEM.7, CN_SYSTEM.8, U$8.25 (25_CVREFOUT/AN10/C3INB/RPB14/SCK1/CTED5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)
SCK3: U$1.3 (03_CLK), U$2.3 (03_CLK), U$3.3 (03_CLK), U$4.3 (03_CLK), U$5.3 (03_CLK), U$6.3 (03_CLK), U$7.3 (03_CLK), U$8.26 (26_AN9/C3INA/RPB15/SCK2/CTED6/PMCS1/RB15), U$9.3 (03_CLK), U$10.3 (03_CLK), U$11.3 (03_CLK), U$12.3 (03_CLK), U$13.3 (03_CLK), U$14.3 (03_CLK), U$15.3 (03_CLK), U$16.3 (03_CLK)
SDI1: CN_KIJ1.4, CN_SYSTEM.11, CN_SYSTEM.12, PROG.4, U$8.14 (14_PGED3/RPB5/PMD7/RB5)
SDI2: PROG.5, R27.2 (E), SW1.G1, SW2.G1, SW3.G1, SW4.G1, SW5.G1, SW6.G1, SW7.G1, SW8.G1, SW9.G1, SW10.G1, SW11.G1, SW12.G1, SW13.G1, SW14.G1, SW17.G1, SW18.G1, SW19.G1, SW20.G1, SW21.G1, SW22.G1, SW23.G1, SW24.G1, SW25.G1, SW26.G1, SW27.G1, SW28.G1, U$8.15 (15_PGEC3/RPB6/PMD6/RB6)
SDO1: CN_SYSTEM.9, CN_SYSTEM.10, U$8.24 (24_AN11/RPB13/CTPLS/PMRD/RB13)
SDO2: U$1.2 (02_SDI), U$10.14 (14_SDO)
SS1: CN_SYSTEM.13, CN_SYSTEM.14, U$8.16 (16_TDI/RPB7/CTED3/PMD5/INT0/RB7)
SS3: U$1.4 (04_!LA!), U$2.4 (04_!LA!), U$3.4 (04_!LA!), U$4.4 (04_!LA!), U$5.4 (04_!LA!), U$6.4 (04_!LA!), U$7.4 (04_!LA!), U$8.21 (21_PGED2/RPB10/CTED11/PMD2/RB10), U$9.4 (04_!LA!), U$10.4 (04_!LA!), U$11.4 (04_!LA!), U$12.4 (04_!LA!), U$13.4 (04_!LA!), U$14.4 (04_!LA!), U$15.4 (04_!LA!), U$16.4 (04_!LA!)

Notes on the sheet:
R28 10k vagy 4k7 fehér led függő

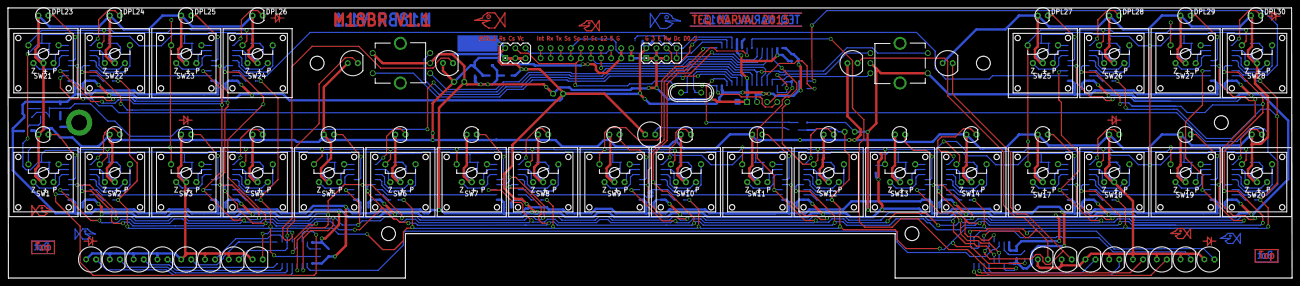
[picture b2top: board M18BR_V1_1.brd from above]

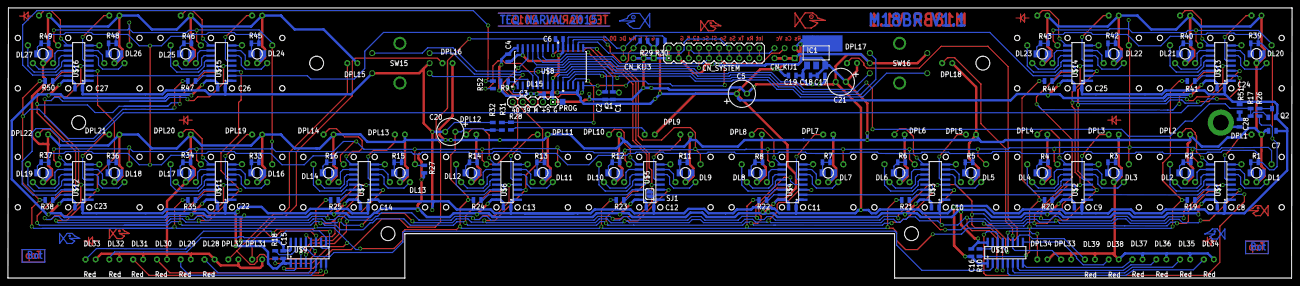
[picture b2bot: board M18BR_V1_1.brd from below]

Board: 2 copper layers, 323.8 x 68.1 mm, 206 parts (127 on the bottom side), 213 nets.
